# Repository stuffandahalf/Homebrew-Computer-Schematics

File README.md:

# Homebrew-Computer-Schematics
The schematics for my homebrew computer

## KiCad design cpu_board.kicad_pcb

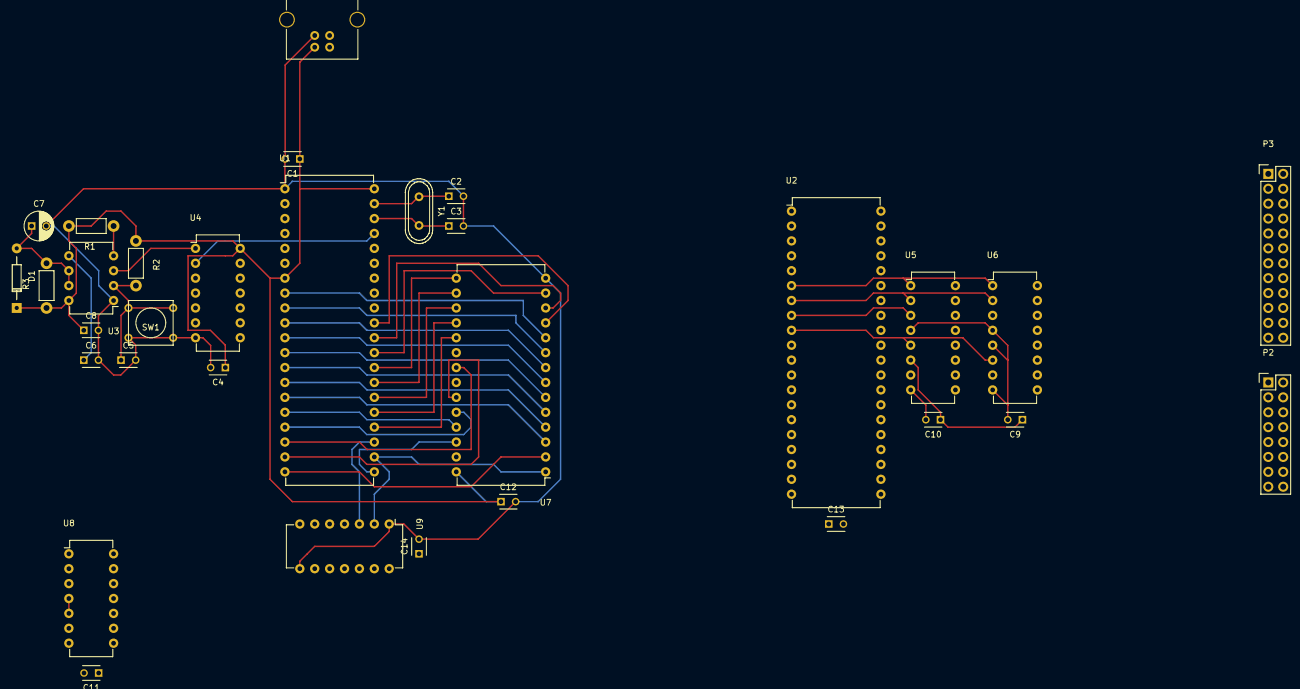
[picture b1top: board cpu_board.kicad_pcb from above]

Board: 2 copper layers, 32 parts (0 on the bottom side), 59 nets.

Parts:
C1, C4, C8, C9, C10, C11, C12, C13, C14: 100nF; C_Disc_D3_P2.5
C2, C3: 24/20/18/15pF; C_Disc_D3_P2.5
C5, C6: 10nF; C_Disc_D3_P2.5
C7: 10uF; C_Radial_D5_L6_P2.5
D1: D; Diode_DO-35_SOD27_Horizontal_RM10
P1: USB_B
P2: CONN_02X08; Pin_Header_Straight_2x08
P3: CONN_02X12; Pin_Header_Straight_2x12
R1: 3.3K; Resistor_Horizontal_RM7mm
R2: 1M; Resistor_Horizontal_RM7mm
R3: 47K; Resistor_Horizontal_RM7mm
SW1: SW_PUSH; SW_PUSH_SMALL
U1: MC6809; DIP-40_W15.24mm
U2: 6821; DIP-40_W15.24mm
U3: NE555; DIP-8_W7.62mm
U4: 74HC04; DIP-14_W7.62mm
U5, U6: 74LS138; DIP-16_W7.62mm
U7: HM62256BLP-7; DIP-28_W15.24mm
U8: 7400; DIP-14_W7.62mm
U9: 74LS139; DIP-14_W7.62mm
Y1: 4/6/8/12MHz; Crystal_HC49-U_Vertical

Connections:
+5V: C1.1, C4.1, C8.1, C9.1, C10.1, C11.1, C12.1, C13.1, C14.1, D1.1, P1.1, P3.1, R1.2, R2.1, R3.1, U1.7, U1.40, U2.20, U3.8, U4.14, U5.6, U5.16, U6.16, U7.28, U8.14
/memory/E: U1.34, U2.25
/memory/R/~W~: U1.32, U2.21
/memory/reset: U1.37, U2.34, U4.2
/memory/rw_control/E: U8.2, U8.10
/memory/rw_control/R/~W~: U8.1, U8.4, U8.5
A0: U1.8, U7.10
A1: U1.9, U7.9
A2: U1.10, U7.8
A3: U1.11, U7.7
A4: U1.12, U7.6
A5: U1.13, U7.5
A6: U1.14, U7.4
A7: U1.15, U7.3
A8: U1.16, U7.25
A9: U1.17, U7.24
A10: U1.18, U7.21
A11: U1.19, U7.23
A12: U1.20, U7.2
A13: U1.21, U7.26
A14: U1.22, U7.1, U9.2
A15: U1.23, U9.3
D0: U1.31, U2.33, U7.11
D1: U1.30, U2.32, U7.12
D2: U1.29, U2.31, U7.13
D3: U1.28, U2.30, U7.15
D4: U1.27, U2.29, U7.16
D5: U1.26, U2.28, U7.17
D6: U1.25, U2.27, U7.18
D7: U1.24, U2.26, U7.19
GND: C1.2, C2.2, C3.2, C4.2, C5.2, C6.2, C7.2, C8.2, C9.2, C10.2, C11.2, C12.2, C13.2, C14.2, P1.4, P3.2, SW1.1, U1.1, U2.1, U3.1, U4.7, U5.4, U5.8, U6.4, U6.5, U6.8, U7.14, U8.7, U9.1, U9.8
unnamed: C2.1, U1.39, Y1.1
unnamed: C3.1, U1.38, Y1.2
unnamed: C5.1, R2.2, SW1.2, U3.2
unnamed: C6.1, U3.5
unnamed: C7.1, D1.2, R3.2, U3.6, U3.7
unnamed: P2.1, U5.15
unnamed: P2.2, U6.15
unnamed: P2.3, U5.14
unnamed: P2.4, U6.14
unnamed: P2.5, U5.13
unnamed: P2.6, U6.13
unnamed: P2.7, U5.12
unnamed: P2.8, U6.12
unnamed: P2.9, U5.11
unnamed: P2.10, U6.11
unnamed: P2.11, U5.10
unnamed: P2.12, U6.10
unnamed: P2.13, U5.9
unnamed: P2.14, U6.9
unnamed: P2.15, U5.7
unnamed: P2.16, U6.7
unnamed: R1.1, U3.4
unnamed: U2.6, U5.1, U6.1
unnamed: U2.7, U5.2, U6.2
unnamed: U2.8, U5.3, U6.3
unnamed: U2.9, U5.5, U6.6
unnamed: U3.3, U4.1
unnamed: U8.6, U8.9

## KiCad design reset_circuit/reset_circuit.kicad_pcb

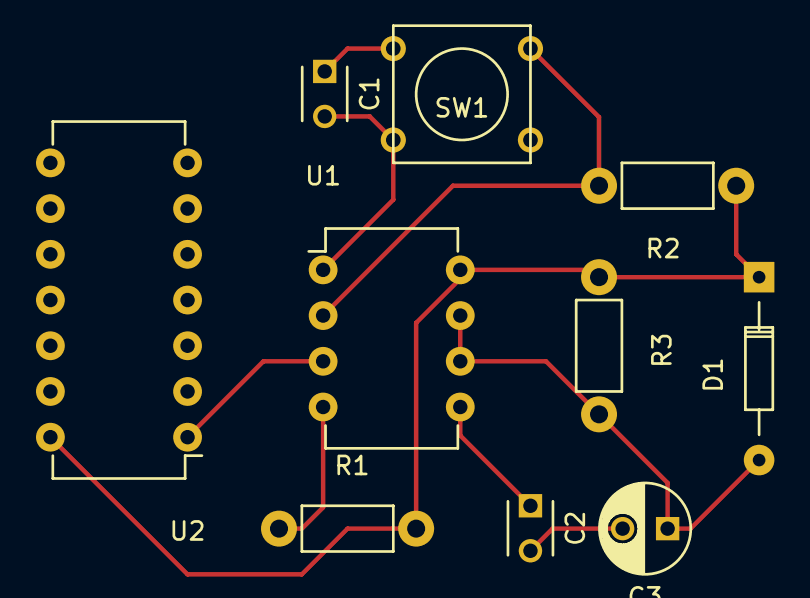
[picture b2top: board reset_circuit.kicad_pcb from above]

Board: 2 copper layers, 10 parts (0 on the bottom side), 7 nets.

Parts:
C1, C2: .01uF; C_Disc_D3_P2.5
C3: 10uF; C_Radial_D5_L6_P2.5
D1: D; Diode_DO-35_SOD27_Horizontal_RM10
R1: 3.3K; Resistor_Horizontal_RM7mm
R2: 1M; Resistor_Horizontal_RM7mm
R3: 47K; Resistor_Horizontal_RM7mm
SW1: SW_PUSH; SW_PUSH_SMALL
U1: NE555; DIP-8_W7.62mm
U2: 74LS04; DIP-14_W7.62mm

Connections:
+5V: D1.1, R1.2, R2.1, R3.1, U1.8, U2.14
GND: C1.2, C2.2, C3.2, SW1.1, U1.1, U2.7
unnamed: C1.1, R2.2, SW1.2, U1.2
unnamed: C2.1, U1.5
unnamed: C3.1, D1.2, R3.2, U1.6, U1.7
unnamed: R1.1, U1.4
unnamed: U1.3, U2.1

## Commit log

2019-02-07 Added reset circuit
2019-02-09 Simplified structure, added new pages
2019-02-10 Added initial banking schematics
2019-02-11 Added more tracks to memory selection
2019-02-20 Replaced descrete logic chips with decoder
